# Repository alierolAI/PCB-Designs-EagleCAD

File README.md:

# PCB Board Designs

Custom PCB shield and board designs developed using Autodesk Eagle CAD.

This repository includes:
- PCB board layouts
- Schematic designs
- Arduino-based shield structures
- Custom Eagle library components

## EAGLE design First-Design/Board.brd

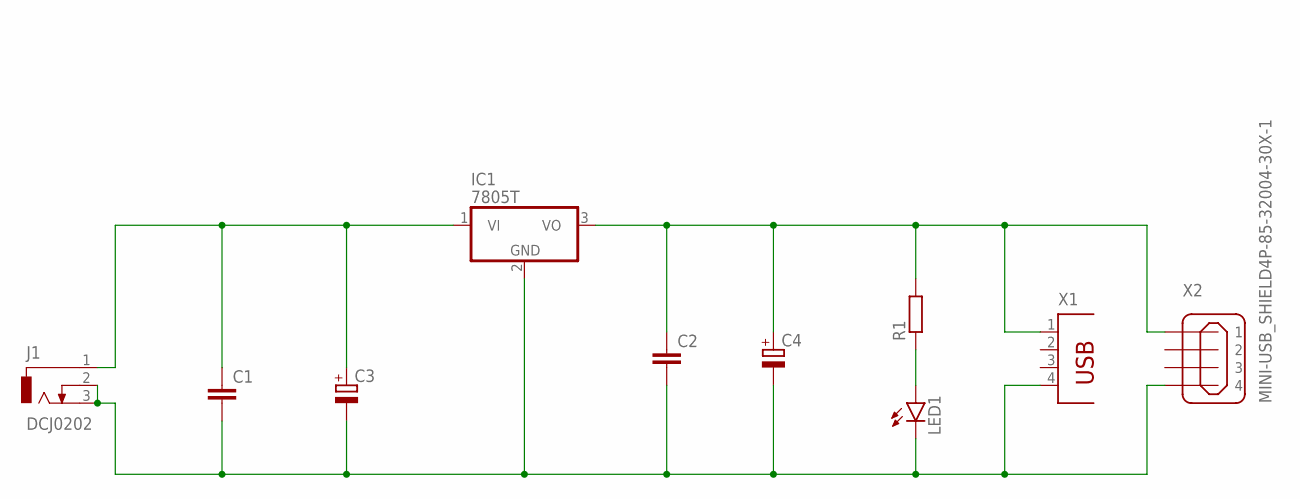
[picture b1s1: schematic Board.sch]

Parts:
C1, C2: C-EU025-024X044; C025-024X044
C3, C4: CPOL-EUB45181A; B45181A
IC1: 7805T; TO220H
J1: DCJ0202
LED1: LED5MM
R1: R-EU_0204/2V; 0204V
X1: PN61729
X2: MINI-USB_SHIELD4P-85-32004-30X-1; 85-32004-30X-1

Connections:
unnamed: C1.1, C3.+, IC1.1 (VI), J1.1
unnamed: C1.2, C2.2, C3.-, C4.-, IC1.2 (GND), J1.2, J1.3, LED1.K (C), X1.4, X2.4
unnamed: C2.1, C4.+, IC1.3 (VO), R1.2, X1.1, X2.1
unnamed: LED1.A, R1.1

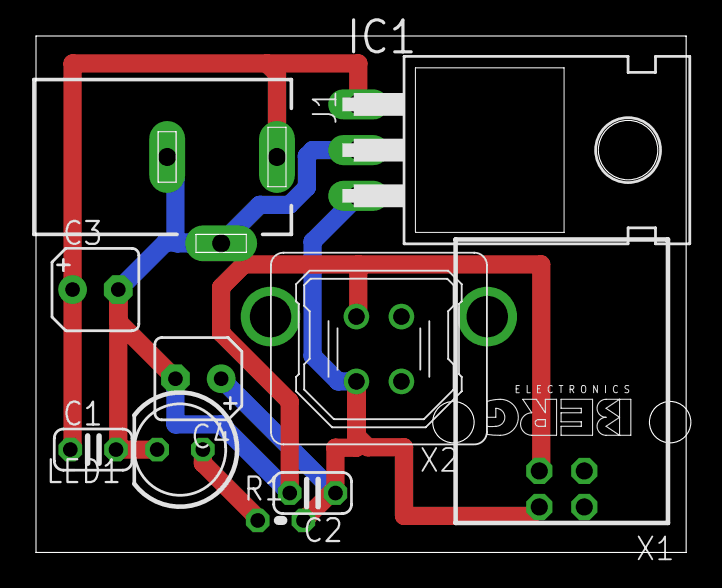
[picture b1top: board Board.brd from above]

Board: 2 copper layers, 36.1 x 28.7 mm, 10 parts (0 on the bottom side), 4 nets.

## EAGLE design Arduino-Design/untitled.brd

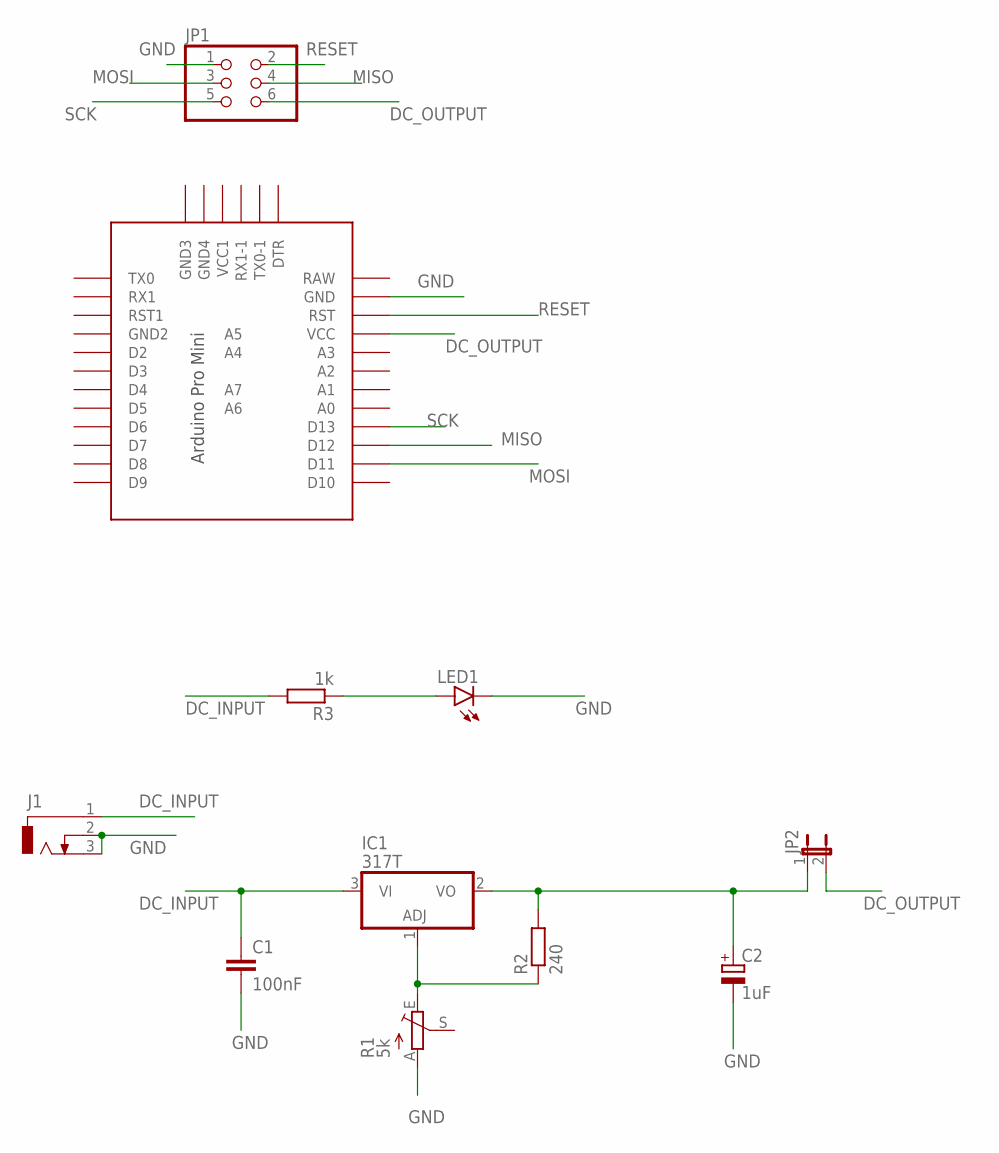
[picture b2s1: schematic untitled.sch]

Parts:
C1: 100nF; C025-025X050
C2: 1uF; E2,5-5
IC1: 317T; TO220H
J1: DCJ0303
JP1: PINHD-2X3; 2X03
JP2: JP1E; JP1
LED1: LED5MM
R1: 5k; S64YW
R2: 240; 0204/5
R3: 1k; 0204/5
U$1: PRO-MINI-2

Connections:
DC_INPUT: C1.1, IC1.3 (VI), J1.1, R3.2
DC_OUTPUT: JP1.6, JP2.2, U$1.VCC
GND: C1.2, C2.-, J1.2, J1.3, JP1.1, LED1.K (C), R1.A, U$1.GND
MISO: JP1.4, U$1.D12
MOSI: JP1.3, U$1.D11
unnamed: IC1.1 (ADJ), R1.E, R2.1
unnamed: C2.+, IC1.2 (VO), JP2.1, R2.2
unnamed: LED1.A, R3.1
RESET: JP1.2, U$1.RST
SCK: JP1.5, U$1.D13

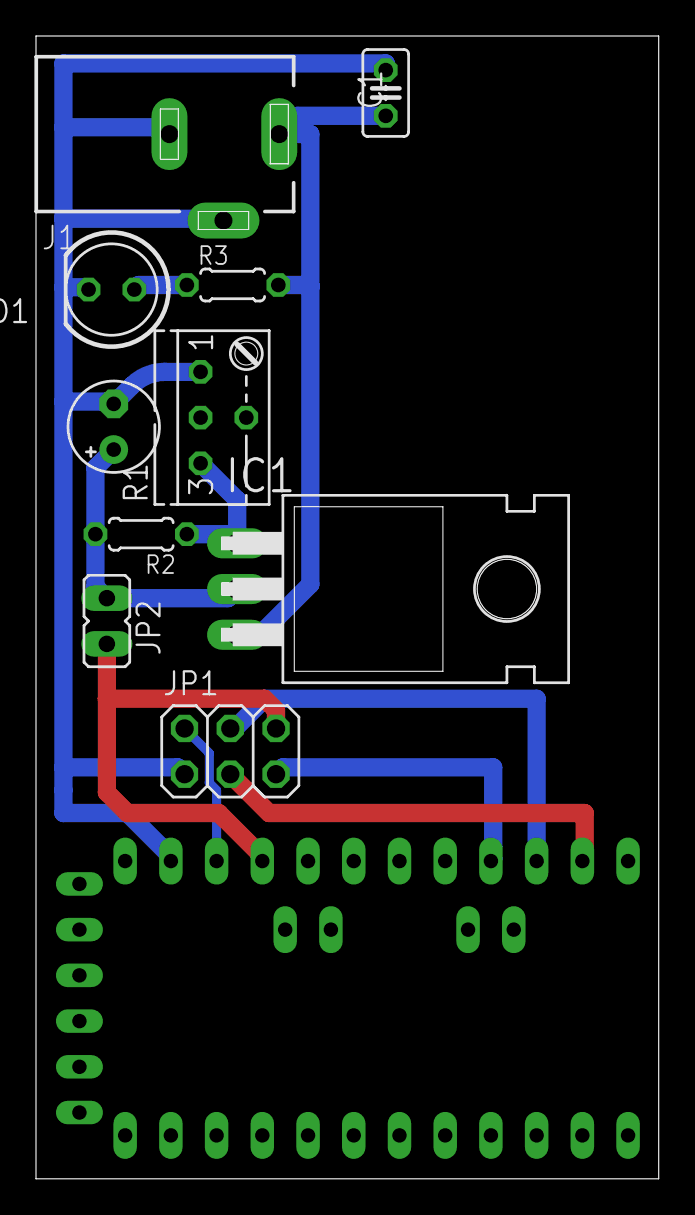
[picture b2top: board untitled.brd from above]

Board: 2 copper layers, 34.6 x 63.5 mm, 11 parts (0 on the bottom side), 10 nets.

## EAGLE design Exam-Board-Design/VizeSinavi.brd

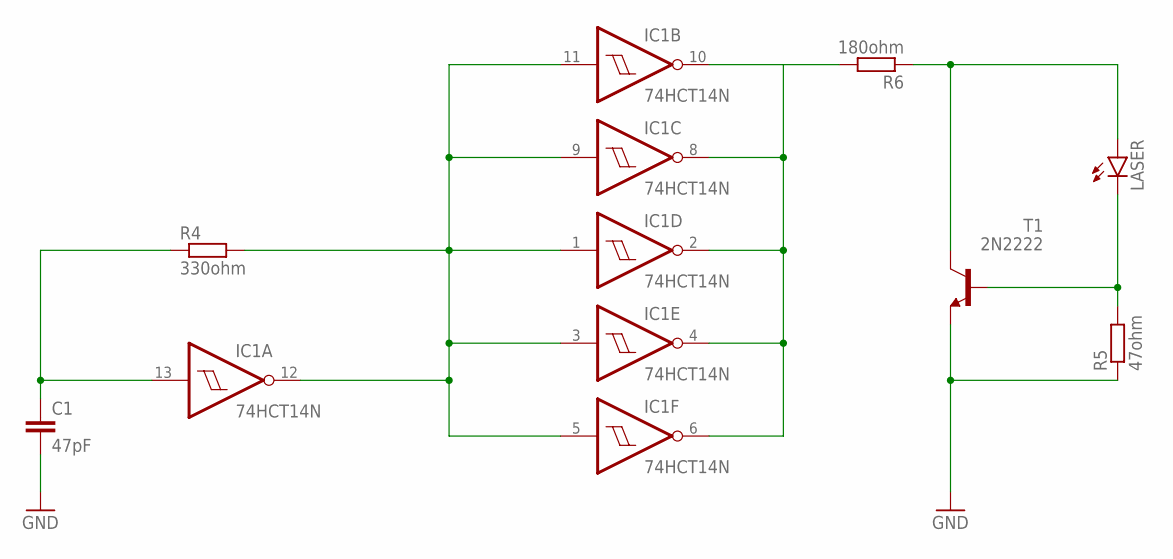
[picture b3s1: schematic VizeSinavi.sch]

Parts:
C1: 47pF; C2.5-3
IC1: 74HCT14N; DIL14
LASER: LED5MM
R4: 330ohm; 0204/5
R5: 47ohm; 0204/5
R6: 180ohm; 0204/5
T1: 2N2222; TO18

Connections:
GND: C1.2, IC1.7 (GND), R5.1, T1.1 (E)
unnamed: C1.1, IC1.13 (I), R4.1
unnamed: IC1.1 (I), IC1.3 (I), IC1.5 (I), IC1.9 (I), IC1.11 (I), IC1.12 (O), R4.2
unnamed: IC1.10 (O), R6.2
unnamed: IC1.2 (O), IC1.4 (O), IC1.6 (O), IC1.8 (O)
unnamed: LASER.A, R6.1, T1.3 (C)
unnamed: LASER.K (C), R5.2, T1.2 (B)
VCC: IC1.14 (VCC)

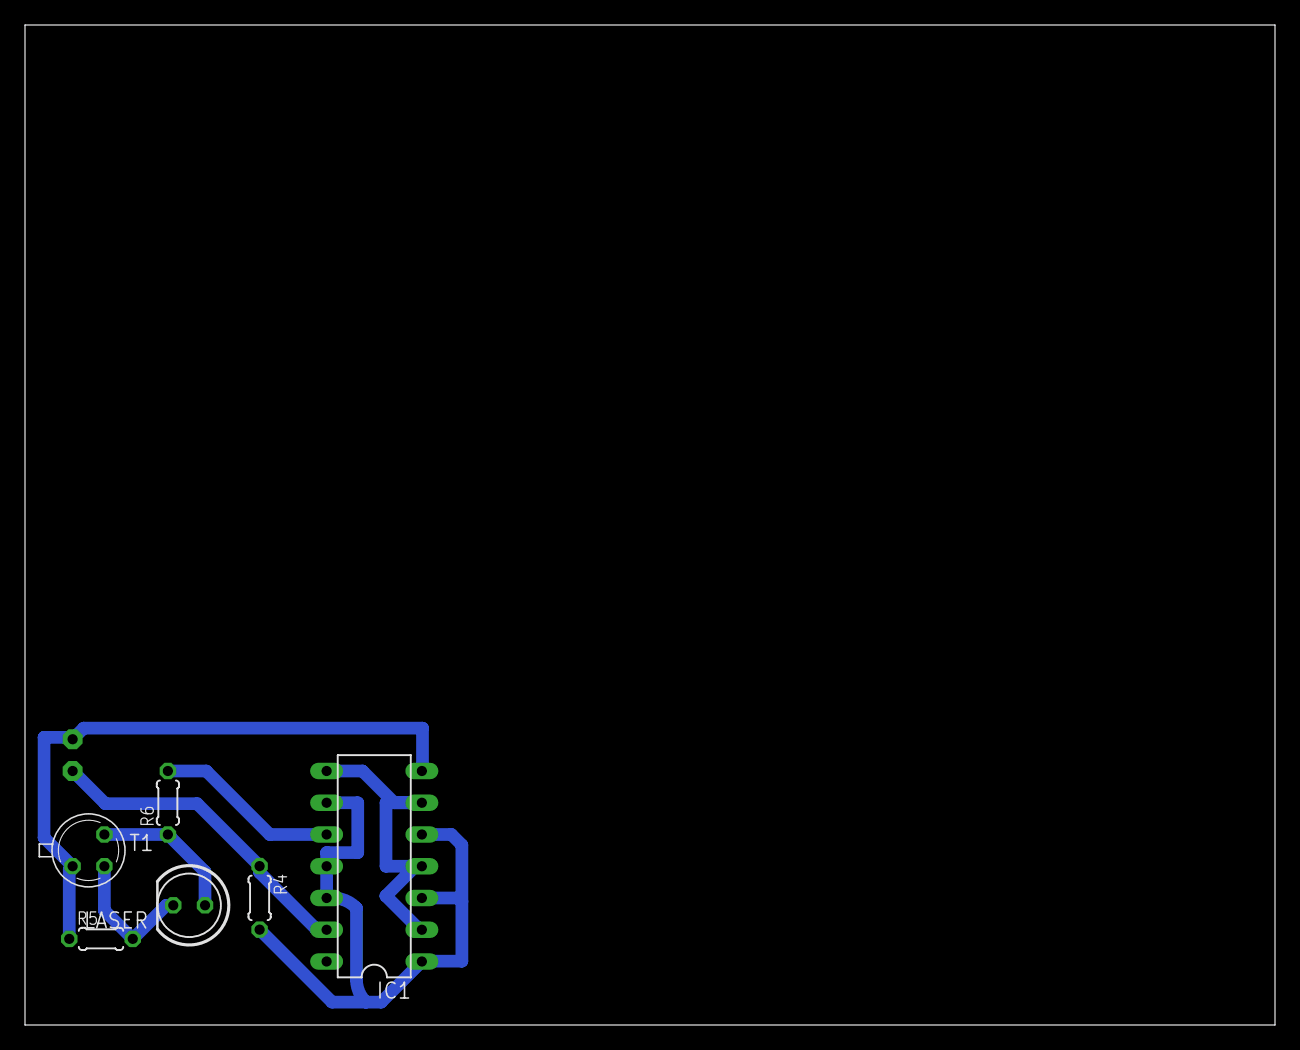
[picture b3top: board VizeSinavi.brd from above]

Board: 2 copper layers, 100.0 x 80.0 mm, 7 parts (1 on the bottom side), 7 nets.

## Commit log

2026-05-09 Add Eagle PCB board and schematic designs
